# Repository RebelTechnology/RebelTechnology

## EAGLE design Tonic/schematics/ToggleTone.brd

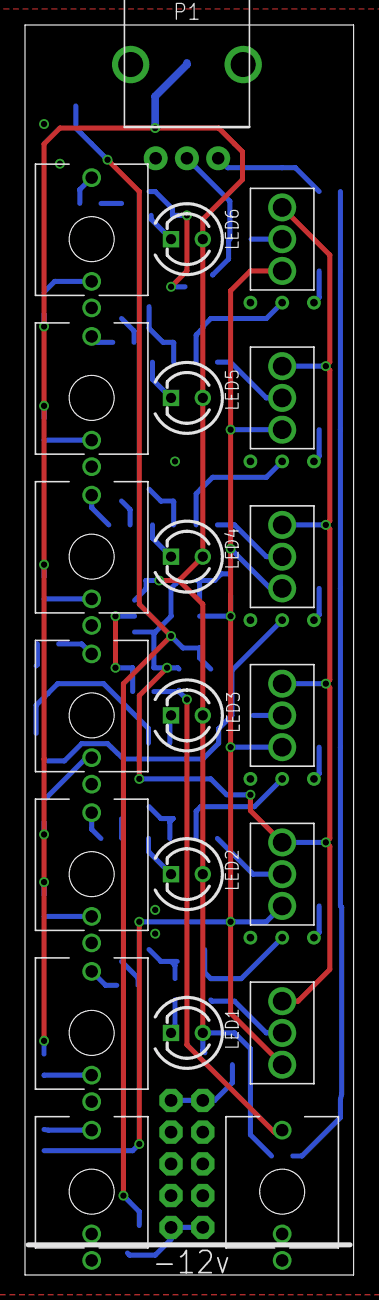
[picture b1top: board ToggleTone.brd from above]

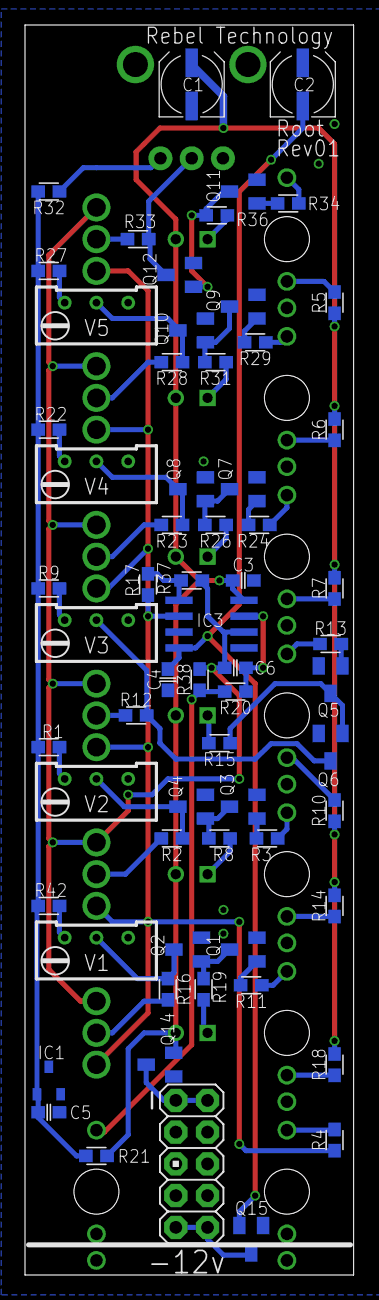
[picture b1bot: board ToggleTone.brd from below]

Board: 2 copper layers, 26.3 x 100.0 mm, 85 parts (64 on the bottom side), 60 nets.

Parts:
C1, C2: 47u; CPOL-5
C3, C4, C5: 100n; C0603
C6: 39p; C0603
IC1: LM4040DIM3-10.0; DBZ_R-PDSO-G3
IC3: TL072D; SO08
IN_1, IN_2, IN_3, IN_4, IN_5, IN_6: THONKICONN
IN_CV: THONKICONN
JP8: M05X2PTH; AVR_ICSP
LED1, LED2, LED3, LED4, LED5, LED6: LED3MM
OUT_CV: THONKICONN
P1: POT-ALPS-RK09L1140
Q1, Q2, Q3, Q4, Q5, Q6, Q7, Q8, Q9, Q10, Q11, Q12, Q15: BSS123; SOT23
Q14: BSS84; SOT23
R1, R9, R18, R42: 51k; 0603
R2, R4, R5, R6, R7, R10, R12, R14, R16, R17, R23, R28, R33, R37, R38: 100k; 0603
R3, R8, R11, R13, R15, R19, R24, R26, R29, R31, R34, R36: 10k; 0603
R20: 1k; 0603
R21: 150R; 0603
R22, R27, R32: 33k; 0603
SW1, SW2, SW3, SW4, SW5, SW6: SUB-MIN-SPDT
V1, V2, V3, V4, V5: RTRIM64W

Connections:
+12V: C1.+, C3.1, IC3.8, LED1.A, LED2.A, LED3.A, LED4.A, LED5.A, LED6.A, Q14.2, R5.2, R6.2, R7.2, R10.2, R14.2, R18.2, R21.2
-12V: C2.-, C4.1, IC3.4, Q15.2
GND: C1.-, C2.+, C3.2, C4.2, C5.2, IC1.2, IC3.3, IC3.5, IN_1.P$1, IN_2.P$1, IN_3.P$1, IN_4.P$1, IN_5.P$1, IN_6.P$1, IN_CV.P$1, IN_CV.P$2, JP8.3, JP8.4, JP8.5, JP8.6, JP8.7, JP8.8, OUT_CV.P$1, OUT_CV.P$2, P1.1, Q1.2, Q2.2, Q3.2, Q4.2, Q5.2, Q6.2, Q7.2, Q8.2, Q9.2, Q10.2, Q11.2, Q12.2, Q14.1, Q15.1, V1.1, V2.1, V3.1, V4.1, V5.1
unnamed: LED1.K, R19.2
unnamed: OUT_CV.P$3, R20.1, R38.1
unnamed: IN_1.P$3, R11.1
unnamed: JP8.9, JP8.10, Q15.3
unnamed: R1.1, V2.3
unnamed: IN_CV.P$3, R4.1
unnamed: Q2.3, R16.2, V1.2
unnamed: LED3.K, R15.2
unnamed: LED4.K, R26.2
unnamed: LED5.K, R31.2
unnamed: LED6.K, R36.2
unnamed: Q3.1, R3.2
unnamed: LED2.K, R8.2
unnamed: IN_1.P$2, R18.1
unnamed: Q3.3, Q4.1, R8.1
unnamed: IN_2.P$3, R3.1
unnamed: Q4.3, R2.2, V2.2
unnamed: C5.1, IC1.1, R1.2, R9.2, R21.1, R22.2, R27.2, R32.2, R42.2
unnamed: Q1.1, R11.2
unnamed: P1.3, R32.1
unnamed: IN_6.P$2, R5.1
unnamed: R9.1, V3.3
unnamed: R12.1, SW3.2
unnamed: Q1.3, Q2.1, R19.1
unnamed: Q5.1, R13.2
unnamed: R16.1, SW1.2
unnamed: Q5.3, Q6.1, R15.1
unnamed: IN_3.P$3, R13.1
unnamed: Q6.3, R12.2, V3.2
unnamed: R2.1, SW2.2
unnamed: R22.1, V4.3
unnamed: C6.1, IC3.7, R20.2
unnamed: Q7.1, R24.2
unnamed: IC3.1, R17.1, R37.2
unnamed: R23.1, SW4.2
unnamed: Q7.3, Q8.1, R26.1
unnamed: IN_4.P$3, R24.1
unnamed: Q8.3, R23.2, V4.2
unnamed: R28.1, SW5.2
unnamed: R33.1, SW6.2
unnamed: IN_5.P$2, R6.1
unnamed: R27.1, V5.3
unnamed: R42.1, V1.3
unnamed: Q9.1, R29.2
unnamed: Q9.3, Q10.1, R31.1
unnamed: IN_2.P$2, R14.1
unnamed: IN_5.P$3, R29.1
unnamed: Q10.3, R28.2, V5.2
unnamed: IN_3.P$2, R10.1
unnamed: Q11.1, R34.2
unnamed: IN_4.P$2, R7.1
unnamed: Q11.3, Q12.1, R36.1
unnamed: IN_6.P$3, R34.1
unnamed: P1.2, Q12.3, R33.2
unnamed: JP8.1, JP8.2, Q14.3
NEG: C6.2, IC3.6, R37.1, R38.2, SW1.3, SW2.3, SW3.3, SW4.3, SW5.3, SW6.3
POS: IC3.2, R4.2, R17.2, SW1.1, SW2.1, SW3.1, SW4.1, SW5.1, SW6.1

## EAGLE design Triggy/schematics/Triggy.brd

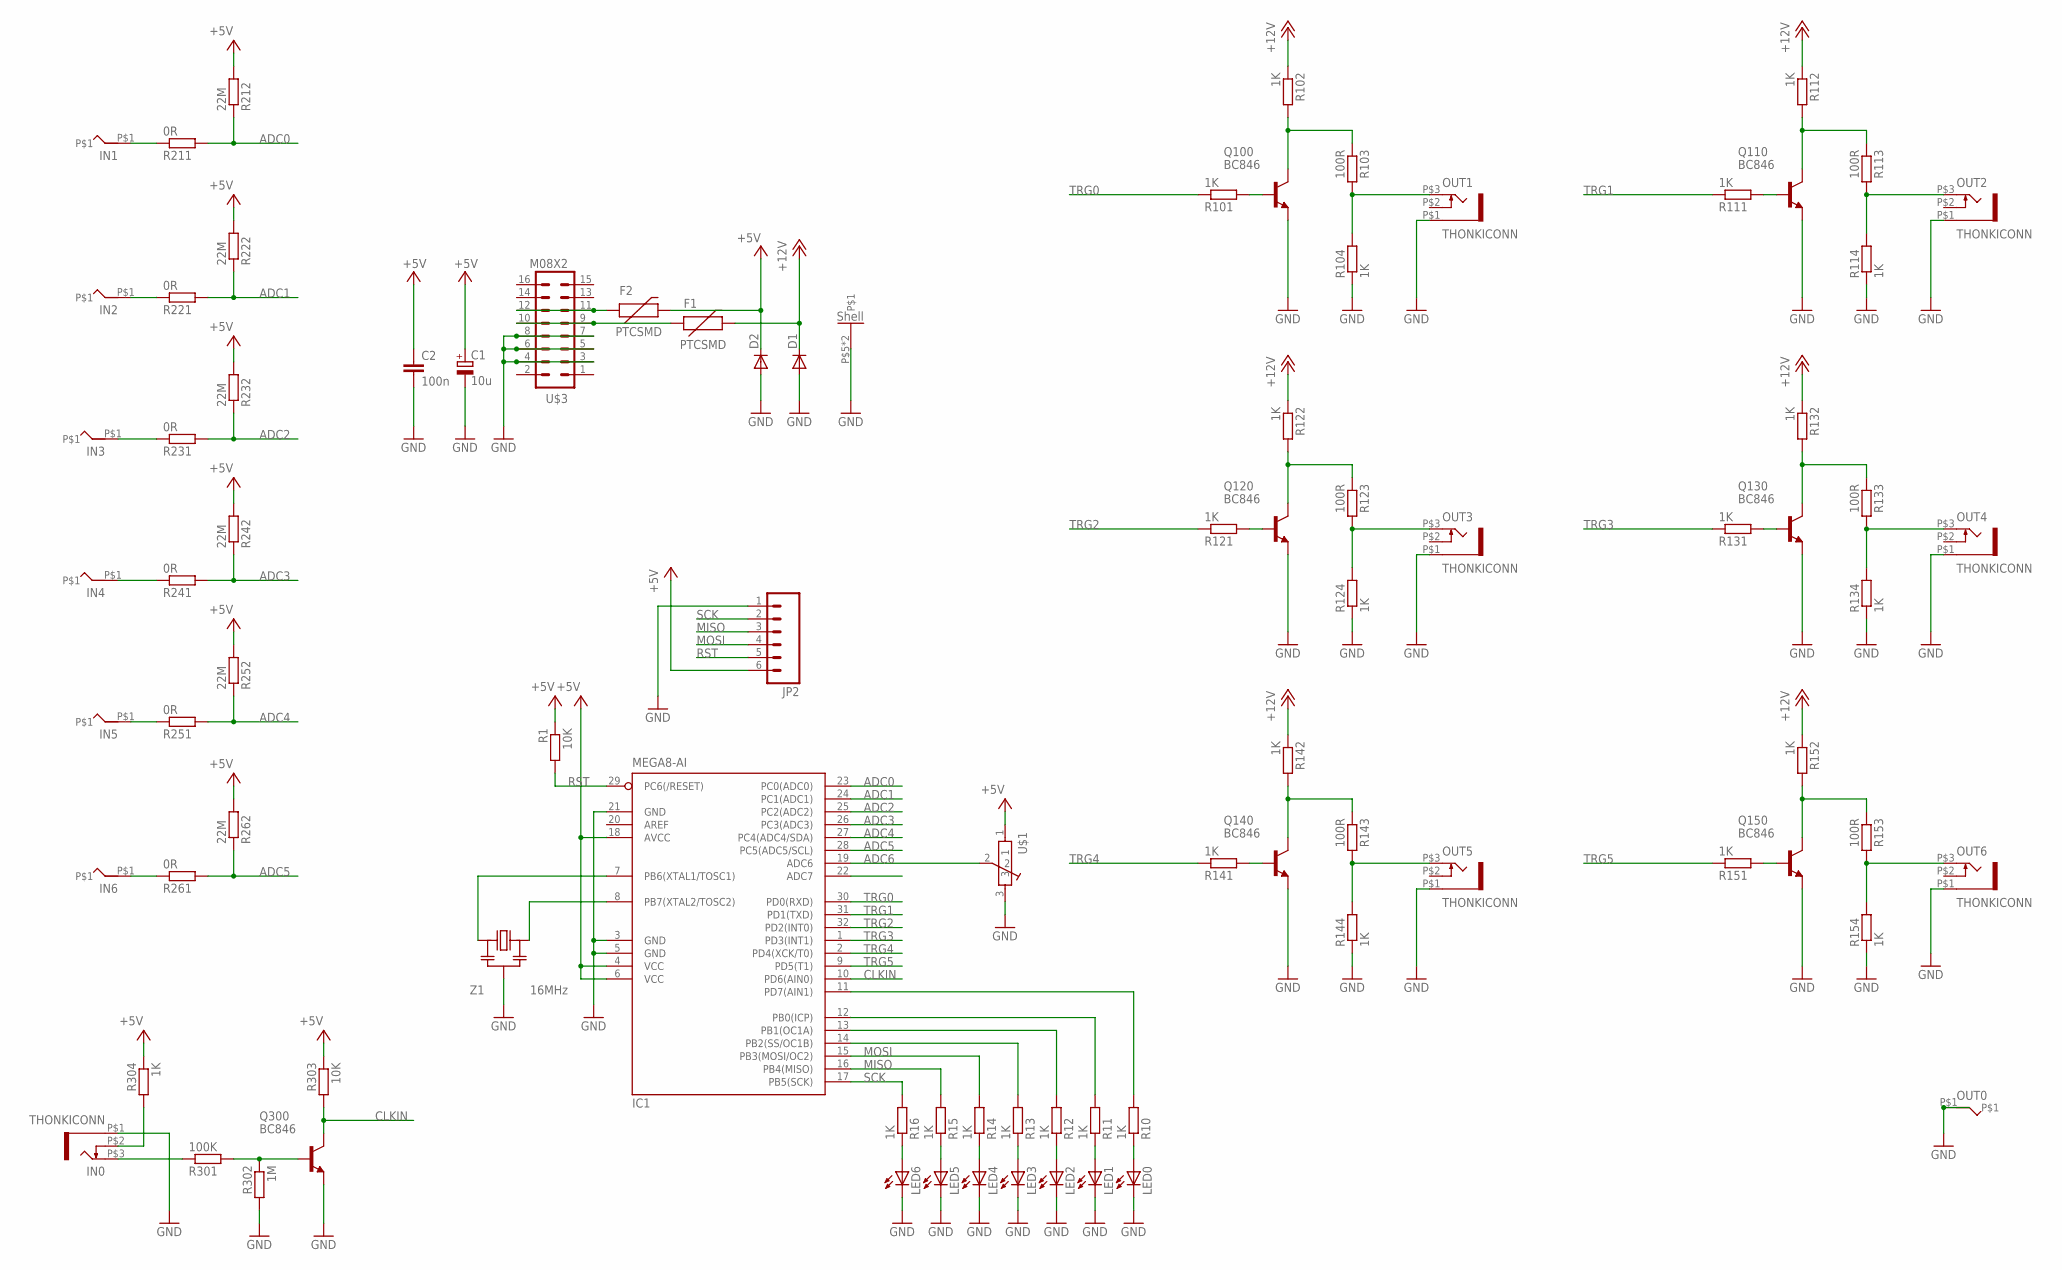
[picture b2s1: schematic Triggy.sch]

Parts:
C1: 10u; E2,5-6
C2: 100n; C0603
D1, D2: DIODESMA; SMA-DIODE
F1, F2: PTCSMD; PTC-1206
IC1: MEGA8-AI; TQFP32-08
IN0: THONKICONN
IN1, IN2, IN3, IN4, IN5, IN6: BANANAJACK
JP2: M06SIP; 1X06
LED0, LED1, LED2, LED3, LED4, LED5, LED6: LED3MM
OUT0: BANANAJACK
OUT1, OUT2, OUT3, OUT4, OUT5, OUT6: THONKICONN
Q100, Q110, Q120, Q130, Q140, Q150, Q300: BC846; SOT23
R1, R303: 10K; 0603
R10, R11, R12, R13, R14, R15, R16, R101, R102, R104, R111, R112, R114, R121, R122, R124, R131, R132, R134, R141, R142, R144, R151, R152, R154, R304: 1K; 0603
R103, R113, R123, R133, R143, R153: 100R; 0603
R211, R221, R231, R241, R251, R261: 0R; 0603
R212, R222, R232, R242, R252, R262: 22M; 0603
R301: 100K; 0603
R302: 1M; 0603
U$1: POT-ALPS-RK09L1140
U$3: M08X2; 2X8
Z1: 16MHz; CSTCE_G_A

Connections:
+5V: C1.+, C2.1, D2.C, F2.2, IC1.4 (VCC), IC1.6 (VCC), IC1.18 (AVCC), JP2.6, R1.1, R212.2, R222.2, R232.2, R242.2, R252.2, R262.2, R303.1, R304.1, U$1.1
+12V: D1.C, F1.2, R102.1, R112.1, R122.1, R132.1, R142.1, R152.1
ADC0: IC1.23 (PC0(ADC0)), R211.2, R212.1
ADC1: IC1.24 (PC1(ADC1)), R221.2, R222.1
ADC2: IC1.25 (PC2(ADC2)), R231.2, R232.1
ADC3: IC1.26 (PC3(ADC3)), R241.2, R242.1
ADC4: IC1.27 (PC4(ADC4/SDA)), R251.2, R252.1
ADC5: IC1.28 (PC5(ADC5/SCL)), R261.2, R262.1
ADC6: IC1.19 (ADC6), U$1.2
ADC7: IC1.22 (ADC7)
CLKIN: IC1.10 (PD6(AIN0)), Q300.3 (C), R303.2
GND: C1.-, C2.2, D1.A, D2.A, IC1.3 (GND), IC1.5 (GND), IC1.21 (GND), IN0.P$1 (5), JP2.1, LED0.K (C), LED1.K (C), LED2.K (C), LED3.K (C), LED4.K (C), LED5.K (C), LED6.K (C), OUT0.P$1, OUT1.P$1 (5), OUT2.P$1 (5), OUT3.P$1 (5), OUT4.P$1 (5), OUT5.P$1 (5), OUT6.P$1 (5), Q100.2 (E), Q110.2 (E), Q120.2 (E), Q130.2 (E), Q140.2 (E), Q150.2 (E), Q300.2 (E), R104.1, R114.1, R124.1, R134.1, R144.1, R154.1, R302.2, U$1.3, U$1.P$5, U$1.P$6, U$3.3, U$3.4, U$3.5, U$3.6, U$3.7, U$3.8, Z1.P$2 (GND)
MISO: IC1.16 (PB4(MISO)), JP2.3, R15.2
MOSI: IC1.15 (PB3(MOSI/OC2)), JP2.4, R14.2
unnamed: IN6.P$1, R261.1
unnamed: F2.1, U$3.11, U$3.12
unnamed: IN2.P$1, R221.1
unnamed: IN4.P$1, R241.1
unnamed: IN0.P$2 (4), R304.2
unnamed: IC1.8 (PB7(XTAL2/TOSC2)), Z1.P$3 (OUT)
unnamed: F1.1, U$3.9, U$3.10
unnamed: IN1.P$1, R211.1
unnamed: IN3.P$1, R231.1
unnamed: LED6.A, R16.1
unnamed: IC1.7 (PB6(XTAL1/TOSC1)), Z1.P$1 (IN)
unnamed: IN5.P$1, R251.1
unnamed: IC1.12 (PB0(ICP)), R11.2
unnamed: Q120.1 (B), R121.2
unnamed: OUT3.P$3 (3), R123.2, R124.2
unnamed: Q120.3 (C), R122.2, R123.1
unnamed: Q140.1 (B), R141.2
unnamed: OUT5.P$3 (3), R143.2, R144.2
unnamed: Q140.3 (C), R142.2, R143.1
unnamed: IC1.13 (PB1(OC1A)), R12.2
unnamed: IC1.14 (PB2(SS/OC1B)), R13.2
unnamed: LED5.A, R15.1
unnamed: Q110.1 (B), R111.2
unnamed: OUT2.P$3 (3), R113.2, R114.2
unnamed: Q110.3 (C), R112.2, R113.1
unnamed: Q130.1 (B), R131.2
unnamed: Q300.1 (B), R301.2, R302.1
unnamed: IN0.P$3 (3), R301.1
unnamed: OUT4.P$3 (3), R133.2, R134.2
unnamed: Q130.3 (C), R132.2, R133.1
unnamed: IC1.11 (PD7(AIN1)), R10.2
unnamed: Q150.1 (B), R151.2
unnamed: Q100.1 (B), R101.2
unnamed: OUT6.P$3 (3), R153.2, R154.2
unnamed: Q150.3 (C), R152.2, R153.1
unnamed: OUT1.P$3 (3), R103.2, R104.2
unnamed: Q100.3 (C), R102.2, R103.1
unnamed: LED4.A, R14.1
unnamed: LED3.A, R13.1
unnamed: LED2.A, R12.1
unnamed: LED1.A, R11.1
unnamed: LED0.A, R10.1
RST: IC1.29 (PC6(/RESET)), JP2.5, R1.2
SCK: IC1.17 (PB5(SCK)), JP2.2, R16.2
TRG0: IC1.30 (PD0(RXD)), R101.1
TRG1: IC1.31 (PD1(TXD)), R111.1
TRG2: IC1.32 (PD2(INT0)), R121.1
TRG3: IC1.1 (PD3(INT1)), R131.1
TRG4: IC1.2 (PD4(XCK/T0)), R141.1
TRG5: IC1.9 (PD5(T1)), R151.1

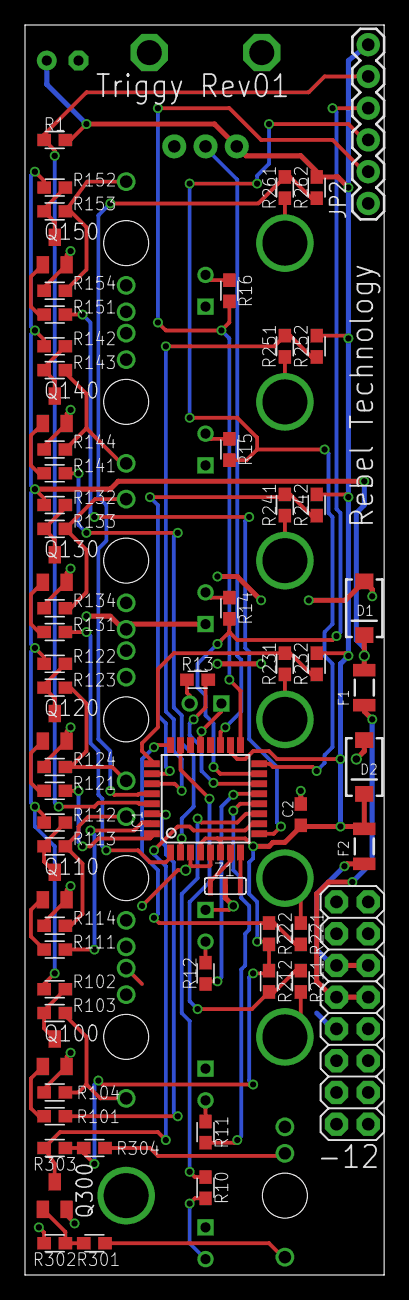
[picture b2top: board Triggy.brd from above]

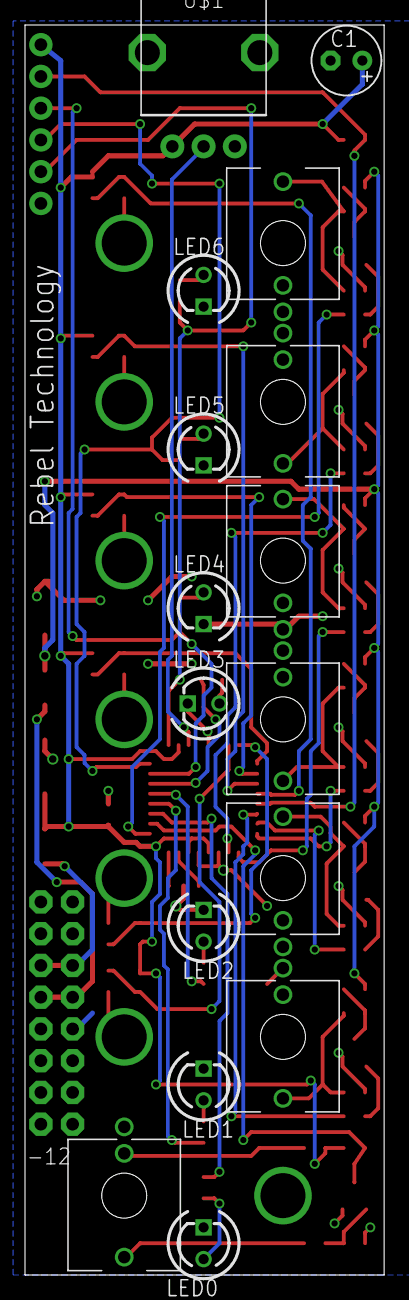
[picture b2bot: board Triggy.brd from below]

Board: 2 copper layers, 28.7 x 100.0 mm, 87 parts (17 on the bottom side), 63 nets.

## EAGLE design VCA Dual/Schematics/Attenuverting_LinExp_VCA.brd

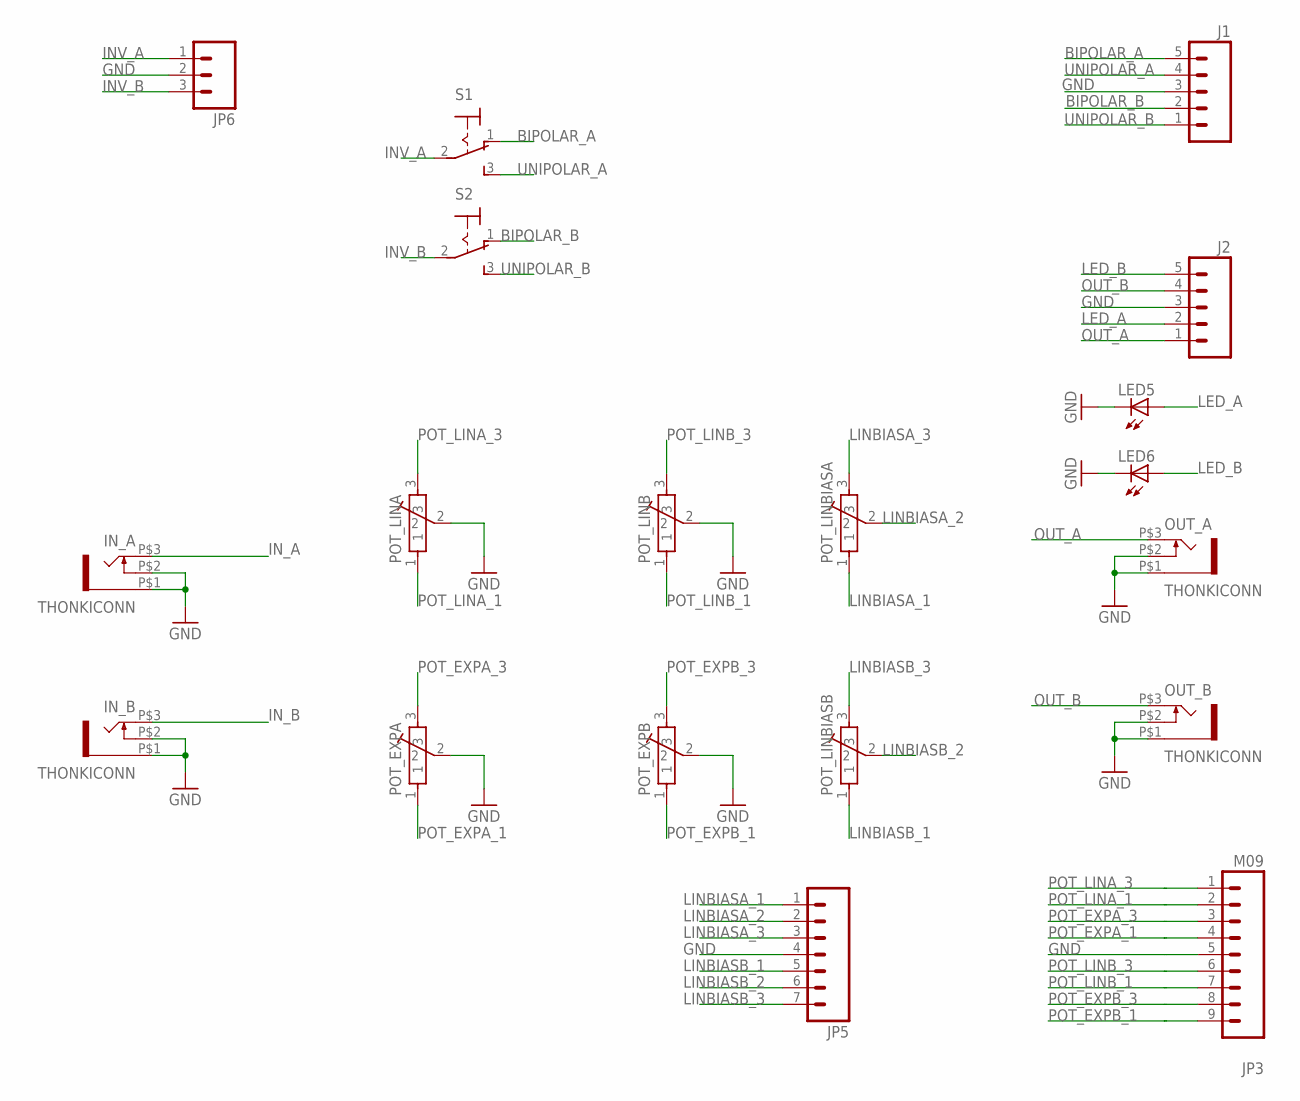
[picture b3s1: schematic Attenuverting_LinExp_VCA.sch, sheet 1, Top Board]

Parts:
IN_A: THONKICONN
IN_B: THONKICONN
J1, J2: M05PTH; 1X05
JP3: M09; 1X09
JP5: M07; 1X07
JP6: M03PTH; 1X03
LED5, LED6: LED3MM
OUT_A: THONKICONN
OUT_B: THONKICONN
POT_EXPA: POT-ALPS-RK09L1140
POT_EXPB: POT-ALPS-RK09L1140
POT_LINA: POT-ALPS-RK09L1140
POT_LINB: POT-ALPS-RK09L1140
POT_LINBIASA: POT-ALPS-RK09L1140
POT_LINBIASB: POT-ALPS-RK09L1140
S1, S2: M9040P

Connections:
BIPOLAR_A: J1.5, S1.1 (O); also elsewhere on the board
BIPOLAR_B: J1.2, S2.1 (O); also elsewhere on the board
GND: IN_A.P$1 (5), IN_A.P$2 (4), IN_B.P$1 (5), IN_B.P$2 (4), J1.3, J2.3, JP3.5, JP5.4, JP6.2, LED5.K (C), LED6.K (C), OUT_A.P$1 (5), OUT_A.P$2 (4), OUT_B.P$1 (5), OUT_B.P$2 (4), POT_EXPA.2, POT_EXPB.2, POT_LINA.2, POT_LINB.2; also elsewhere on the board
INV_A: JP6.1, S1.2; also elsewhere on the board
INV_B: JP6.3, S2.2; also elsewhere on the board
IN_A: IN_A.P$3 (3); also elsewhere on the board
IN_B: IN_B.P$3 (3); also elsewhere on the board
LED_A: J2.2, LED5.A; also elsewhere on the board
LED_B: J2.5, LED6.A; also elsewhere on the board
LINBIASA_1: JP5.1, POT_LINBIASA.1; also elsewhere on the board
LINBIASA_2: JP5.2, POT_LINBIASA.2; also elsewhere on the board
LINBIASA_3: JP5.3, POT_LINBIASA.3; also elsewhere on the board
LINBIASB_1: JP5.5, POT_LINBIASB.1; also elsewhere on the board
LINBIASB_2: JP5.6, POT_LINBIASB.2; also elsewhere on the board
LINBIASB_3: JP5.7, POT_LINBIASB.3; also elsewhere on the board
OUT_A: J2.1, OUT_A.P$3 (3); also elsewhere on the board
OUT_B: J2.4, OUT_B.P$3 (3); also elsewhere on the board
POT_EXPA_1: JP3.4, POT_EXPA.1; also elsewhere on the board
POT_EXPA_3: JP3.3, POT_EXPA.3; also elsewhere on the board
POT_EXPB_1: JP3.9, POT_EXPB.1; also elsewhere on the board
POT_EXPB_3: JP3.8, POT_EXPB.3; also elsewhere on the board
POT_LINA_1: JP3.2, POT_LINA.1; also elsewhere on the board
POT_LINA_3: JP3.1, POT_LINA.3; also elsewhere on the board
POT_LINB_1: JP3.7, POT_LINB.1; also elsewhere on the board
POT_LINB_3: JP3.6, POT_LINB.3; also elsewhere on the board
UNIPOLAR_A: J1.4, S1.3 (S); also elsewhere on the board
UNIPOLAR_B: J1.1, S2.3 (S); also elsewhere on the board

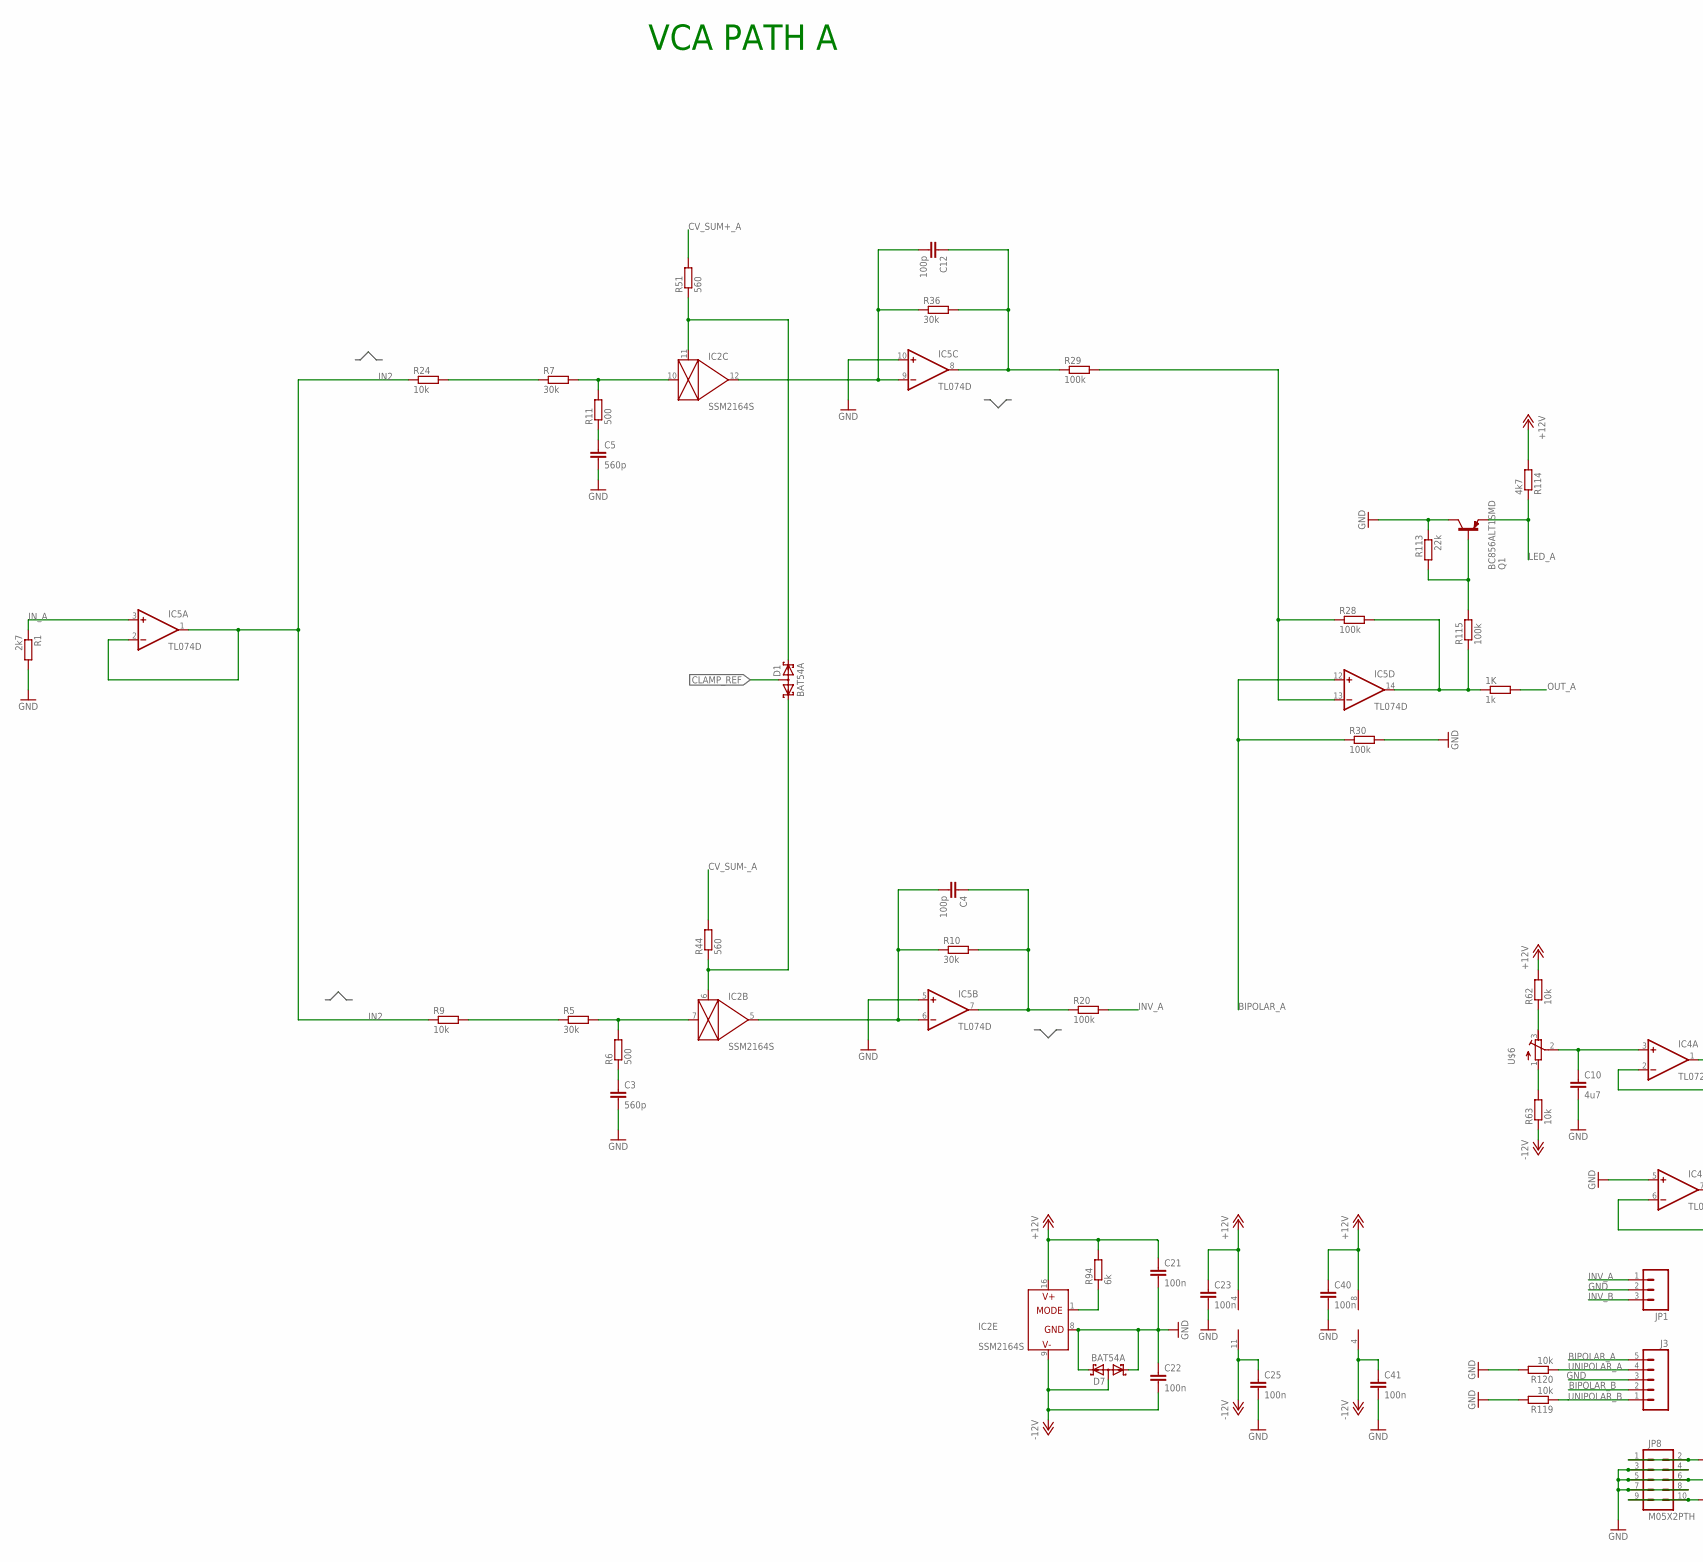
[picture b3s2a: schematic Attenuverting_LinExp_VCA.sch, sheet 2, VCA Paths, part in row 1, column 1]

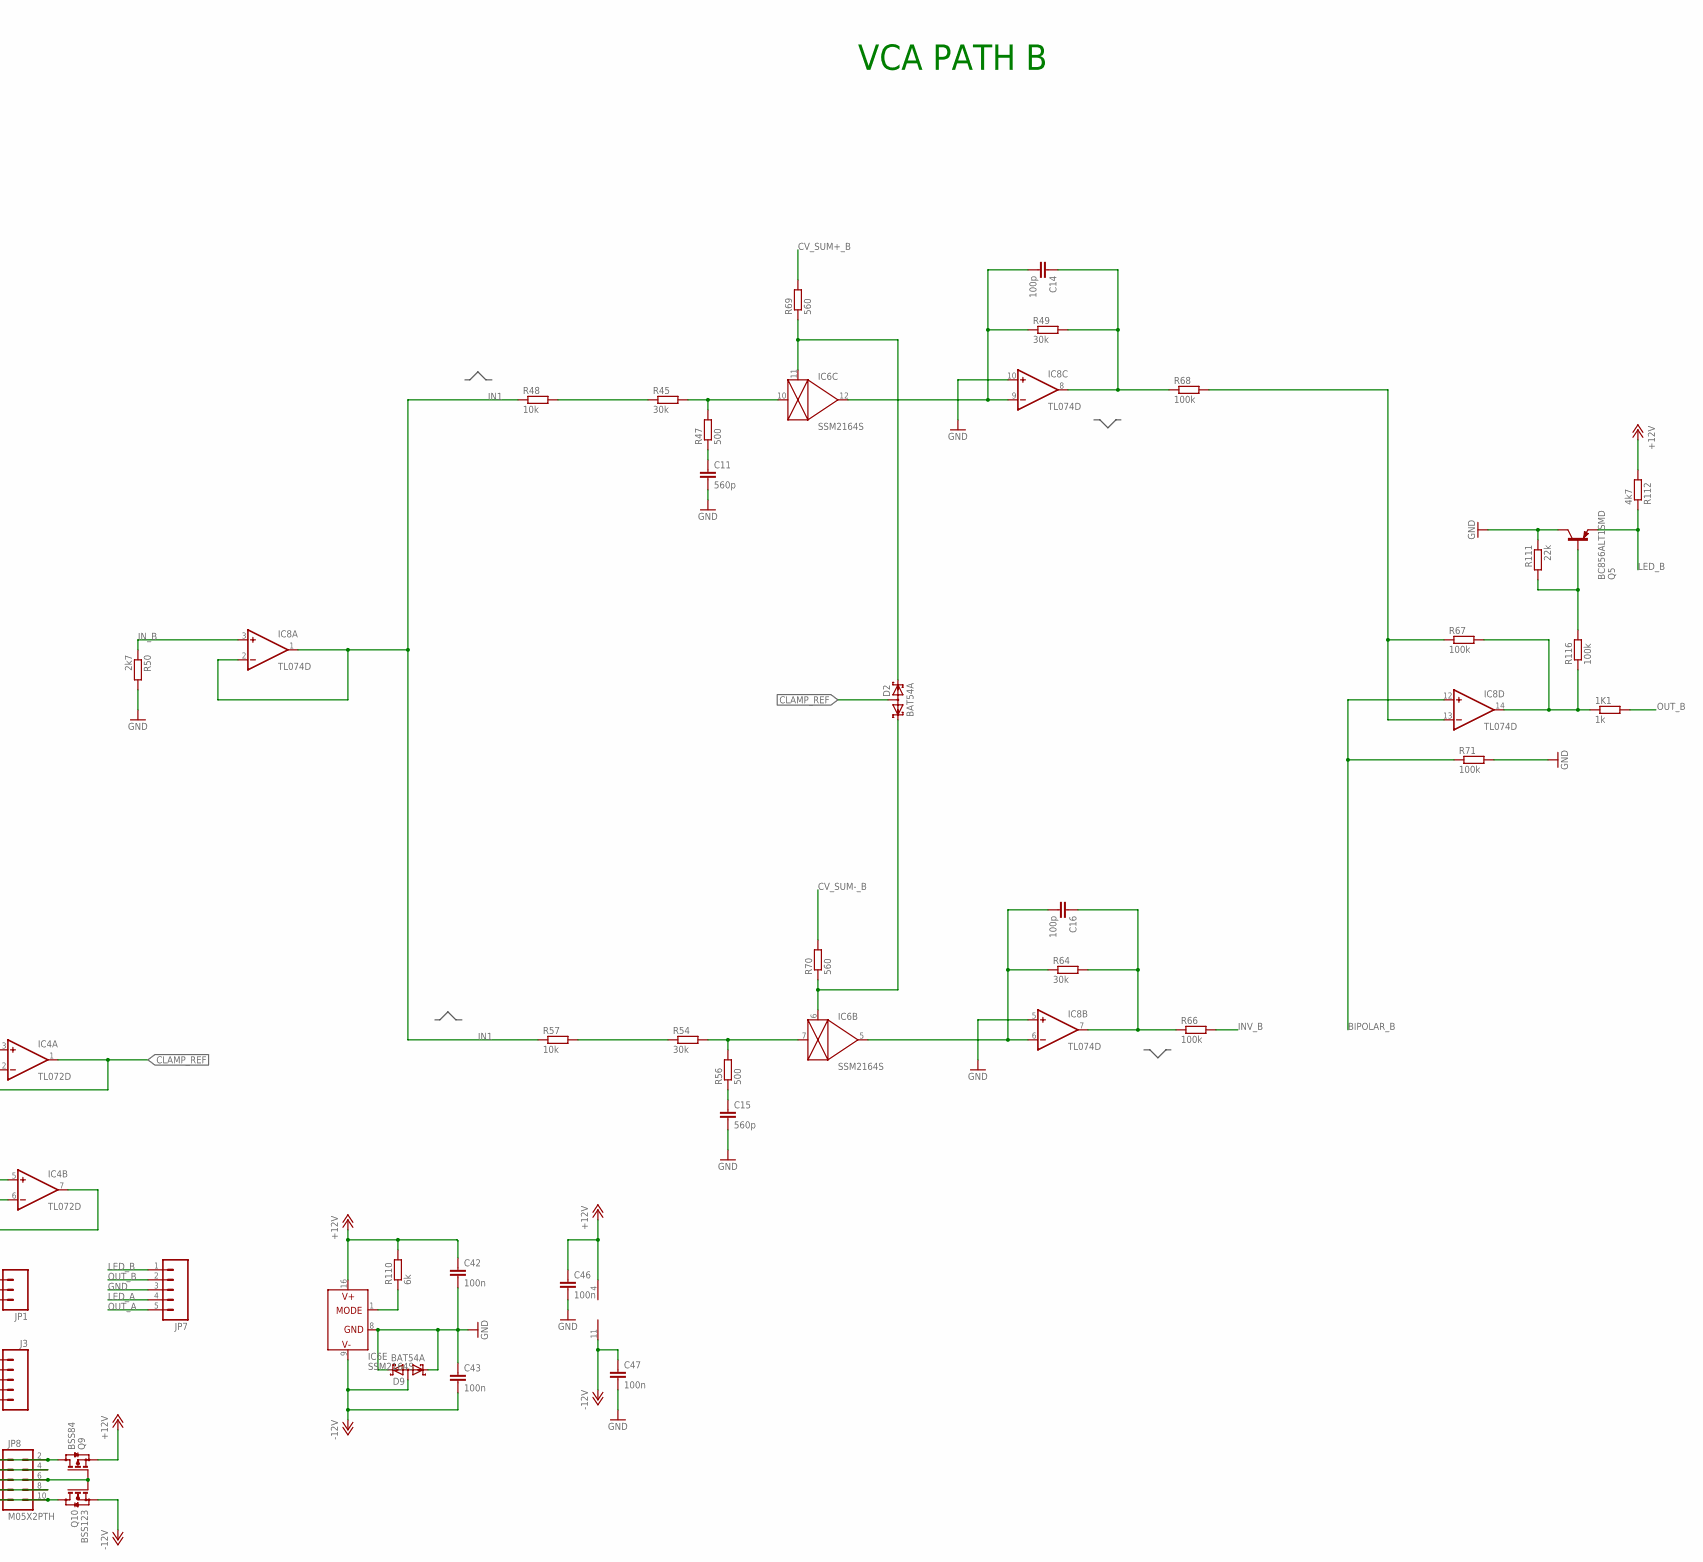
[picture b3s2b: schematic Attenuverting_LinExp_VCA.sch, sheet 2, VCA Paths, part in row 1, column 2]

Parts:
1K, 1K1: 1k; 0603; MPN MC0063W06031160K
C3, C5, C11, C15: 560p; C0603K
C4, C12, C14, C16: 100p; C0603K
C10: 4u7; C0603K
C21, C22, C23, C25, C40, C41, C42, C43, C46, C47: 100n; C0603K
D1, D2, D7, D9: BAT54A; SOT23
IC2, IC6: SSM2164S; SOIC16N
IC4: TL072D; SO08
IC5, IC8: TL074D; SO14
J3: M05PTH; 1X05
JP1: M03PTH; 1X03
JP7: M05PTH; 1X05
JP8: M05X2PTH; AVR_ICSP
Q1, Q5: BC856ALT1SMD; SOT23-BEC
Q9: BSS84; SOT23
Q10: BSS123; SOT23
R1, R50: 2k7; 0603
R5, R7, R10, R36, R45, R49, R54, R64: 30k; 0603
R6, R11, R47, R56: 500; 0603
R9, R24, R48, R57, R62, R63, R119, R120: 10k; 0603
R20, R28, R29, R30, R66, R67, R68, R71, R115, R116: 100k; 0603
R44, R51, R69, R70: 560; 0603
R94, R110: 6k; 0603
R111, R113: 22k; 0603
R112, R114: 4k7; 0603
U$6: R-TRIMM64W; RTRIM64W

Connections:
+12V: C21.1, C23.1, C40.1, C42.1, C46.1, IC2.16 (V+), IC4.8 (V+), IC5.4 (V+), IC6.16 (V+), IC8.4 (V+), Q9.2 (S), R62.2, R94.2, R110.2, R112.2, R114.2; also elsewhere on the board
-12V: C22.2, C25.1, C41.1, C43.2, C47.1, D7.3 (AA), D9.3 (AA), IC2.9 (V-), IC4.4 (V-), IC5.11 (V-), IC6.9 (V-), IC8.11 (V-), Q10.2 (S), R63.1; also elsewhere on the board
BIPOLAR_A: IC5.12 (+IN), J3.5, R30.1; also elsewhere on the board
BIPOLAR_B: IC8.12 (+IN), J3.2, R71.1; also elsewhere on the board
CLAMP_REF: D1.3 (AA), D2.3 (AA), IC4.1 (OUT), IC4.2 (-IN)
CV_SUM+_A: R51.2; also elsewhere on the board
CV_SUM+_B: R69.2; also elsewhere on the board
CV_SUM-_A: R44.2; also elsewhere on the board
CV_SUM-_B: R70.2; also elsewhere on the board
DELETENET: R119.1
GND: C3.2, C5.2, C10.2, C11.2, C15.2, C21.2, C22.1, C23.2, C25.2, C40.2, C41.2, C42.2, C43.1, C46.2, C47.2, D7.1 (K1), D7.2 (K2), D9.1 (K1), D9.2 (K2), IC2.8 (GND), IC4.5 (+IN), IC5.5 (+IN), IC5.10 (+IN), IC6.8 (GND), IC8.5 (+IN), IC8.10 (+IN), J3.3, JP1.2, JP7.3, JP8.3, JP8.4, JP8.5, JP8.6, JP8.7, JP8.8, Q1.C, Q5.C, Q9.1 (G), Q10.1 (G), R1.2, R30.2, R50.2, R71.2, R111.1, R113.1, R119.2, R120.2; also elsewhere on the board
IC2B_1: D2.1 (K1), IC6.6 (CTRL), R70.1
IC2B_6: D1.1 (K1), IC2.6 (CTRL), R44.1
IC2C_1: D2.2 (K2), IC6.11 (CTRL), R69.1
IC2C_11: D1.2 (K2), IC2.11 (CTRL), R51.1
IN1: IC8.1 (OUT), IC8.2 (-IN), R48.1, R57.1
IN2: IC5.1 (OUT), IC5.2 (-IN), R9.1, R24.1
INV_A: JP1.1, R20.2; also elsewhere on the board
INV_B: JP1.3, R66.2; also elsewhere on the board
IN_A: IC5.3 (+IN), R1.1; also elsewhere on the board
IN_B: IC8.3 (+IN), R50.1; also elsewhere on the board
LED_A: JP7.4, Q1.E, R114.1; also elsewhere on the board
LED_B: JP7.1, Q5.E, R112.1; also elsewhere on the board
unnamed: JP8.9, JP8.10, Q10.3 (D)
unnamed: C3.1, R6.1
unnamed: JP8.1, JP8.2, Q9.3 (D)
unnamed: IC5.13 (-IN), R28.1, R29.2
unnamed: IC2.7 (IN), R5.2, R6.2
unnamed: R5.1, R9.2
unnamed: C5.1, R11.1
unnamed: C4.2, IC2.5 (OUT), IC5.6 (-IN), R10.1
unnamed: C4.1, IC5.7 (OUT), R10.2, R20.1
unnamed: IC2.10 (IN), R7.2, R11.2
unnamed: 1K.1, IC5.14 (OUT), R28.2, R115.1
unnamed: C11.1, R47.1
unnamed: R7.1, R24.2
unnamed: IC6.10 (IN), R45.2, R47.2
unnamed: R62.1, U$6.3 (E)
unnamed: Q5.B, R111.2, R116.2
unnamed: R45.1, R48.2
unnamed: C14.2, IC6.12 (OUT), IC8.9 (-IN), R49.1
unnamed: C14.1, IC8.8 (OUT), R49.2, R68.1
unnamed: C15.1, R56.1
unnamed: IC6.7 (IN), R54.2, R56.2
unnamed: C12.2, IC2.12 (OUT), IC5.9 (-IN), R36.1
unnamed: R54.1, R57.2
unnamed: C12.1, IC5.8 (OUT), R29.1, R36.2
unnamed: C16.2, IC6.5 (OUT), IC8.6 (-IN), R64.1
unnamed: R63.2, U$6.1 (A)
unnamed: C10.1, IC4.3 (+IN), U$6.2 (S)
unnamed: C16.1, IC8.7 (OUT), R64.2, R66.1
unnamed: IC8.13 (-IN), R67.1, R68.2
unnamed: 1K1.1, IC8.14 (OUT), R67.2, R116.1
unnamed: IC2.1 (MODE), R94.1
unnamed: IC4.6 (-IN), IC4.7 (OUT)
unnamed: Q1.B, R113.2, R115.2
unnamed: IC6.1 (MODE), R110.1
OUT_A: 1K.2, JP7.5; also elsewhere on the board
OUT_B: 1K1.2, JP7.2; also elsewhere on the board
UNIPOLAR_A: J3.4, R120.1; also elsewhere on the board
UNIPOLAR_B: J3.1; also elsewhere on the board

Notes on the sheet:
VCA PATH A
VCA PATH B

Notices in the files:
parts and their libraries:
SparkFun: Licensing: CC v3.0 Share-Alike You are welcome to use this library for commercial purposes.
SparkFun-Connectors: Licensing: Creative Commons ShareAlike 4.0 International - https://creativecommons.org/licenses/by-sa/4.0
